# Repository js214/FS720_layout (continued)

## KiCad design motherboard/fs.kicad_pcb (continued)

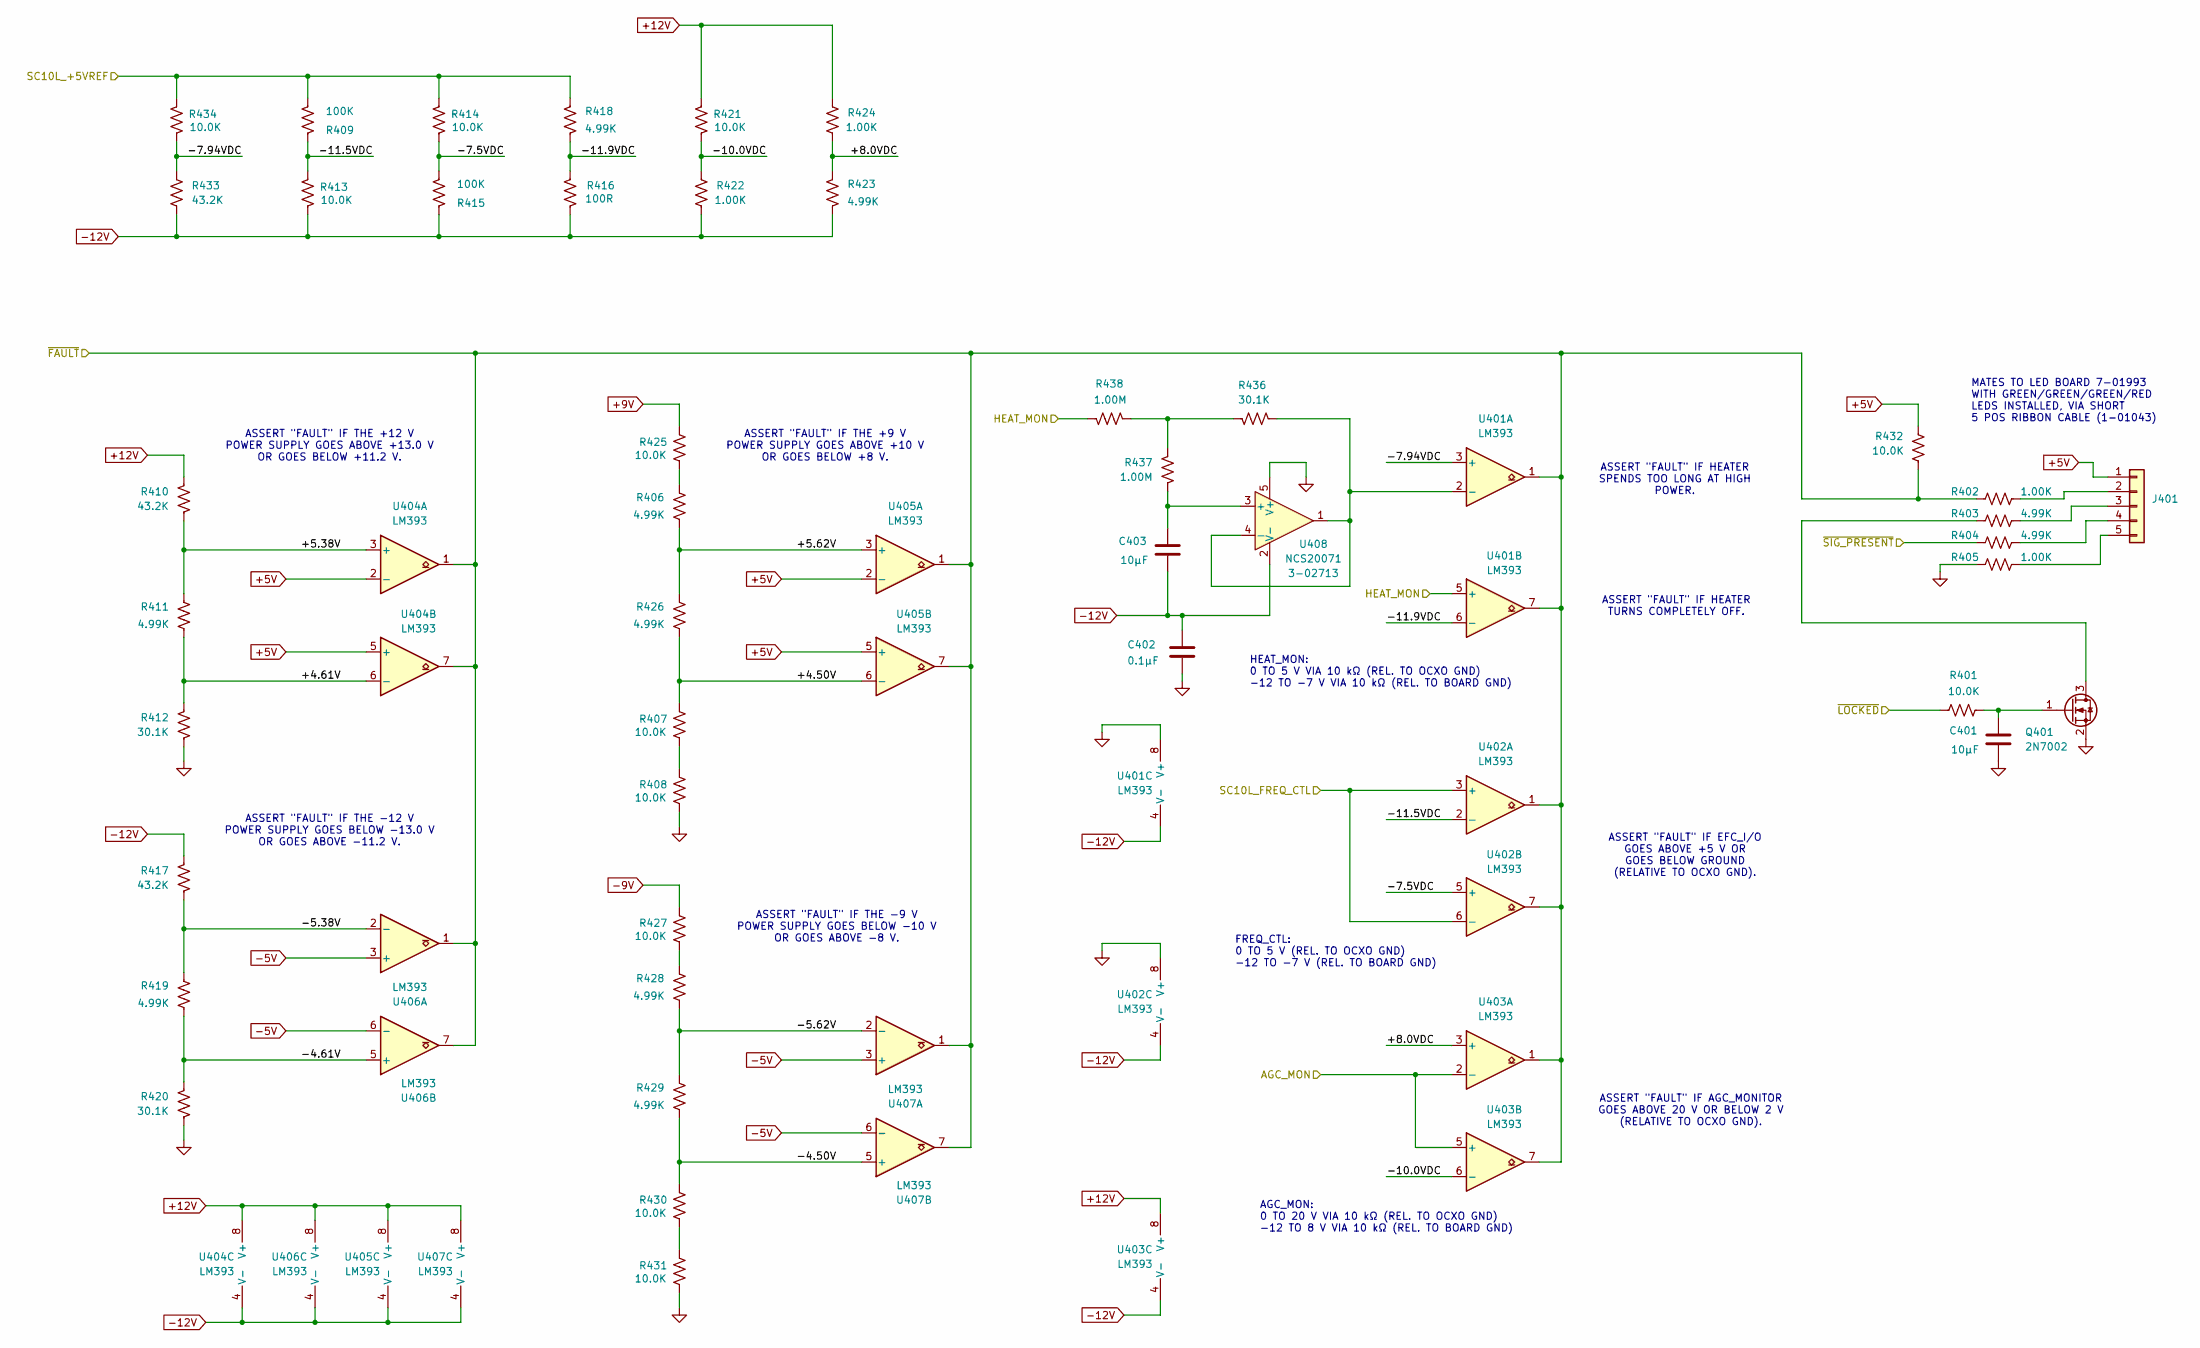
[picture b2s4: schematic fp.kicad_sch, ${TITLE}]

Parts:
C401, C403: 10μF; C_0805_2012Metric; Voltage 25V; MPN GRM21BR61E106KA73L; JLCPCB C84416
C402: 0.1μF; C_0603_1608Metric; Voltage 50V; MPN 06035C104KAT4A; JLCPCB C14663
J401: Conn_01x05; PinHeader_1x05_P2.54mm_Vertical; MPN --; JLCPCB --
Q401: 2N7002; SOT-23; MPN 2N7002H6327XTSA2; JLCPCB C8545
R401, R407, R408, R413, R414, R421, R425, R427, R430, R431, R432, R434: 10.0K; R_0603_1608Metric; MPN TFCR0603-16W-E-1002FT; JLCPCB C98220
R402, R405, R422, R424: 1.00K; R_0603_1608Metric; MPN RR0816P-102-D; JLCPCB C22548
R403, R404, R406, R411, R418, R419, R423, R426, R428, R429: 4.99K; R_0603_1608Metric; MPN TFCR0603-16W-E-4991FT; JLCPCB C23046
R409, R415: 100K; R_0603_1608Metric; MPN TFCR0603-16W-E-1003FT; JLCPCB C25803
R410, R417, R433: 43.2K; R_0603_1608Metric; MPN TNPW060343K2BEEA; JLCPCB C23053
R412, R420, R436: 30.1K; R_0603_1608Metric; MPN RR0816P-3012-D-47C; JLCPCB C23000
R416: 100R; R_0603_1608Metric; MPN RR0816P-101-D; JLCPCB C22775
R437, R438: 1.00M; R_0603_1608Metric; MPN RMCF0603FT1M00; JLCPCB C22935
U401, U402, U403, U404, U405, U406, U407: LM393; SO-8_3.9x4.9mm_P1.27mm; MPN LM393DR; JLCPCB C67470
U408: NCS20071; TSOT-23-5; MPN NCS20071SN2T1G; JLCPCB C457774

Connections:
+5V: J401.1, R432.1, U404.2 (-), U404.5 (+), U405.2 (-), U405.5 (+); also elsewhere on the board
+9V: R425.1; also elsewhere on the board
+12V: R410.2, R421.1, R424.2, U403.8 (V+), U404.8 (V+), U405.8 (V+), U406.8 (V+), U407.8 (V+); also elsewhere on the board
-5V: U406.3 (+), U406.6 (-), U407.3 (+), U407.6 (-); also elsewhere on the board
-9V: R427.1; also elsewhere on the board
-12V: C402.1, C403.2, R413.2, R415.1, R416.2, R417.2, R422.1, R423.1, R433.1, U401.4 (V-), U402.4 (V-), U403.4 (V-), U404.4 (V-), U405.4 (V-), U406.4 (V-), U407.4 (V-), U408.2 (V-); also elsewhere on the board
/AGC_MON: U403.2 (-), U403.5 (+); also elsewhere on the board
/Front Panel/+4.50V: R407.1, R426.1, U405.6 (-)
/Front Panel/+4.61V: R411.1, R412.2, U404.6 (-)
/Front Panel/+5.38V: R410.1, R411.2, U404.3 (+)
/Front Panel/+5.62V: R406.1, R426.2, U405.3 (+)
/Front Panel/+8.0VDC: R423.2, R424.1, U403.3 (+)
/Front Panel/-4.50V: R429.1, R430.1, U407.5 (+)
/Front Panel/-4.61V: R419.1, R420.2, U406.5 (+)
/Front Panel/-5.38V: R417.1, R419.2, U406.2 (-)
/Front Panel/-5.62V: R428.1, R429.2, U407.2 (-)
/Front Panel/-7.5VDC: R414.2, R415.2, U402.5 (+)
/Front Panel/-7.94VDC: R433.2, R434.2, U401.3 (+)
/Front Panel/-10.0VDC: R421.2, R422.2, U403.6 (-)
/Front Panel/-11.5VDC: R409.1, R413.1, U402.2 (-)
/Front Panel/-11.9VDC: R416.1, R418.1, U401.6 (-)
/HEAT_MON: R438.2, U401.5 (+); also elsewhere on the board
/SC10L_+5VREF: R409.2, R414.1, R418.2, R434.1; also elsewhere on the board
/SC10L_FREQ_CTL: U402.3 (+), U402.6 (-); also elsewhere on the board
/~FAULT: R402.1, R432.2, U401.1, U401.7, U402.1, U402.7, U403.1, U403.7, U404.1, U404.7, U405.1, U405.7, U406.1, U406.7, U407.1, U407.7; also elsewhere on the board
/~LOCKED: R401.1; also elsewhere on the board
/~SIG_PRESENT: R404.1; also elsewhere on the board
GND: C401.2, C402.2, Q401.2 (S), R405.1, R408.2, R412.1, R420.1, R431.2, U401.8 (V+), U402.8 (V+), U408.5 (V+); also elsewhere on the board
unnamed: J401.2, R402.2
unnamed: J401.3, R403.2
unnamed: J401.4, R404.2
unnamed: J401.5, R405.2
unnamed: Q401.3 (D), R403.1
unnamed: C401.1, Q401.1 (G), R401.2
unnamed: R406.2, R425.2
unnamed: R407.2, R408.1
unnamed: R427.2, R428.2
unnamed: R430.2, R431.1
unnamed: R436.1, R437.2, R438.1
unnamed: R436.2, U401.2 (-), U408.1, U408.4 (-)
unnamed: C403.1, R437.1, U408.3 (+)

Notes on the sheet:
ASSERT "FAULT" IF THE -12 V POWER SUPPLY GOES BELOW -13.0 V OR GOES ABOVE -11.2 V.
AGC_MON: 0 TO 20 V VIA 10 kΩ (REL. TO OCXO GND) -12 TO 8 V VIA 10 kΩ (REL. TO BOARD GND)
ASSERT "FAULT" IF EFC_I/O GOES ABOVE +5 V OR GOES BELOW GROUND (RELATIVE TO OCXO GND).
ASSERT "FAULT" IF THE +12 V POWER SUPPLY GOES ABOVE +13.0 V OR GOES BELOW +11.2 V.
ASSERT "FAULT" IF THE -9 V POWER SUPPLY GOES BELOW -10 V OR GOES ABOVE -8 V.
HEAT_MON: 0 TO 5 V VIA 10 kΩ (REL. TO OCXO GND) -12 TO -7 V VIA 10 kΩ (REL. TO BOARD GND)
ASSERT "FAULT" IF HEATER SPENDS TOO LONG AT HIGH POWER.
ASSERT "FAULT" IF THE +9 V POWER SUPPLY GOES ABOVE +10 V OR GOES BELOW +8 V.
ASSERT "FAULT" IF HEATER TURNS COMPLETELY OFF.
FREQ_CTL: 0 TO 5 V (REL. TO OCXO GND) -12 TO -7 V (REL. TO BOARD GND)
MATES TO LED BOARD 7-01993 WITH GREEN/GREEN/GREEN/RED LEDS INSTALLED, VIA SHORT 5 POS RIBBON CABLE (1-01043)
ASSERT "FAULT" IF AGC_MONITOR GOES ABOVE 20 V OR BELOW 2 V (RELATIVE TO OCXO GND).

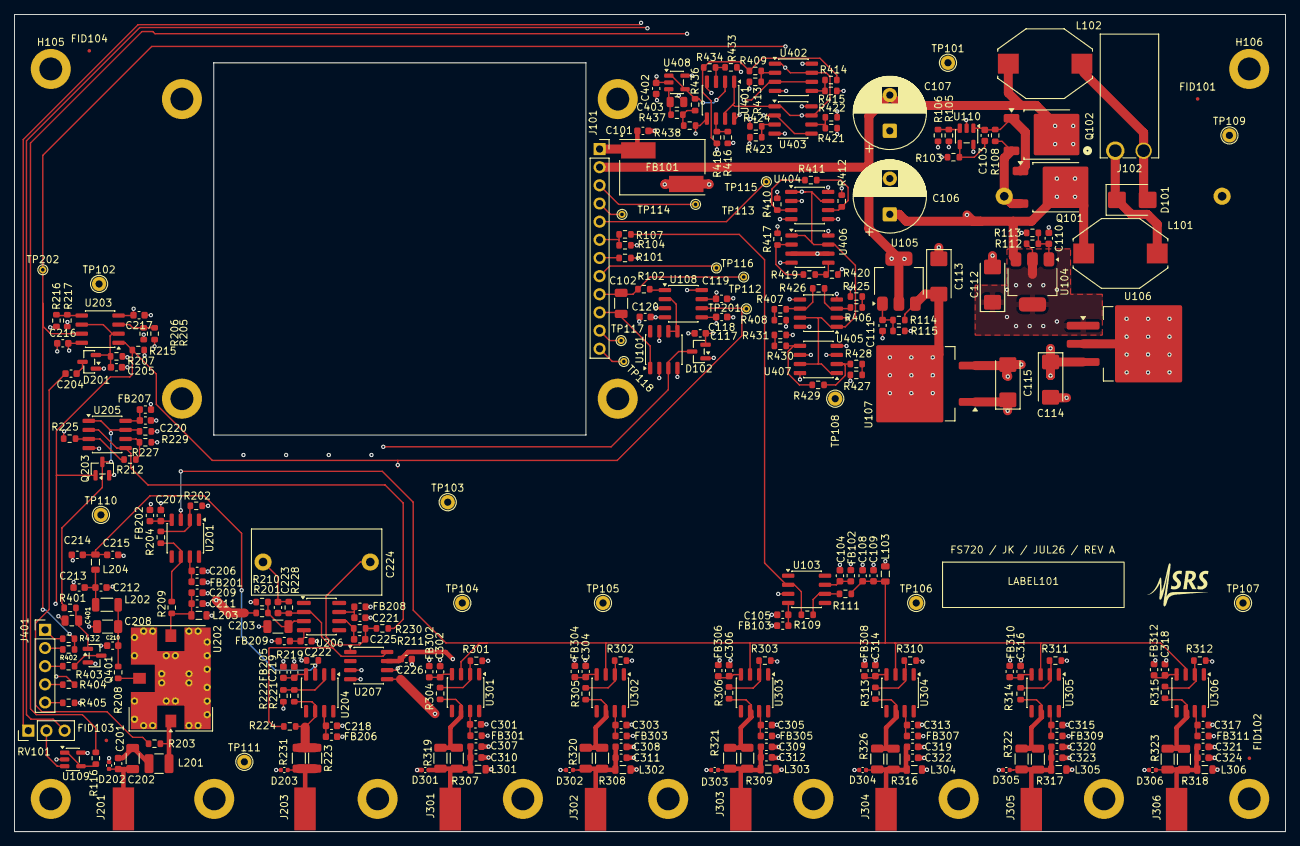
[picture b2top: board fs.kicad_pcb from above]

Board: 6 copper layers, 177.8 x 114.3 mm, 307 parts (1 on the bottom side), 128 nets.

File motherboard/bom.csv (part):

"Designator","Qty","Value","Exclude from BOM","Footprint","MPN","JLCPCB Part #","SRS PN","Voltage","Description"
"C101,C104,C105,C110,C111,C117,C118,C119,C120,C205,C206,C207,C216,C217,C218,C219,C220,C221,C222,C226,C301,C302,C303,C304,C305,C306,C313,C314,C315,C316,C317,C318,C402","33","0.1μF","","Capacitor_SMD:C_0603_1608Metric","06035C104KAT4A","C14663","5-00764","50V","Capacitor, Mono, 50V,+/-10%, X7R, 0603"
"C102,C203","2","0.1μF C0G","","Capacitor_SMD:C_1206_3216Metric","GRT31C5C1H104FA02L","C3839854","5-01075","50V","Cap Ceramic 0.1uF 50V C0G 1% Pad SMD 1206 125°C Automotive AEC-Q200 T/R"
"C103,C204,C212,C214,C223,C225","6","1nF NP0","","Capacitor_SMD:C_0603_1608Metric","C0603C102J5GACTU","C2181873","5-00740","50V","Capacitor, Mono, 50V, ¦0.25pF or 5%, NPO, 0603, 1000P"
"C106,C107","2","330μF","","Capacitor_THT:CP_Radial_D10.0mm_P5.00mm","EEU-FC1V331","EEU-FC1V331","5-00516","35V","Capacitor, Electrolytic, High Ripple, High Temp (-55/+105 DEG C)"
"C108,C209,C307,C308,C309,C319,C320,C321","8","47pF","","Capacitor_SMD:C_0603_1608Metric","C0603C470J5GACTU","C2167347","5-00708","50V","Capacitor, Mono, 50V, ¦0.25pF or 5%, NPO, 0603"
"C109,C211,C310,C311,C312,C322,C323,C324","8","120pF","","Capacitor_SMD:C_0603_1608Metric","C0603C121J5GACTU","C2168575","5-00718","50V","CAP CER 120PF 50V C0G/NP0 0603"
"C112,C113,C114,C115","4","4.7μF-T35","","Capacitor_Tantalum_SMD:CP_EIA-6032-15_Kemet-U","TAJC475M035RNJ","C11378","5-00520","35V","SMD TANTALUM, C-Case"
"C201,C213","2","270pF","","Capacitor_SMD:C_0603_1608Metric","C0603C271J5GACTU","C49326315","5-00726","50V","Capacitor, Mono, 50V, ¦0.25pF or 5%, NPO, 0603"
"C202,C208","2","180pF","","Capacitor_SMD:C_1206_3216Metric","C1206C181J5GACTU","C541494","5-00378","50V","Capacitor, Mono, 50V, 5%, NPO, 1206"
"C210","1","100pF","","Capacitor_SMD:C_0603_1608Metric","C0603C101J5GACTU","C2167328","5-00716","50V","Capacitor, Mono, 50V, ¦0.25pF or 5%, NPO, 0603"
"C215","1","390pF","","Capacitor_SMD:C_0603_1608Metric","C0603C391J5GACTU","C22408867","5-00730","50V","Capacitor, Mono, 50V, ¦0.25pF or 5%, NPO, 0603"
"C224","1","10μF PET","","Capacitor_THT:C_Rect_L18.0mm_W9.0mm_P15.00mm_FKS3_FKP3","B32522C0106K189","C3769153","5-00959","63V","10uF Polyester Cap"
"C401,C403","2","10μF","","Capacitor_SMD:C_0805_2012Metric","GRM21BR61E106KA73L","C84416","5-00954","25V","10 uF 0805 capacitor, 25V X5R 10%"
"D101","1","MBRS230LT3G","","Diode_SMD:D_SMB","MBRS230LT3G  ","C236135","3-02091","","DIODE Schottky 30V 2A"
"D102,D201","2","MMBD352LT1G","","Package_TO_SOT_SMD:SOT-23","MMBD352LT1G","C463549","3-00538","","MMBD352L, DUAL SCHOTTKY DIODE"
"D202,D203,D301,D302,D303,D304,D305,D306","8","14V TVS","","Capacitor_SMD:C_0402_1005Metric","PESD0402-140","C7473167","3-02609","","TVS DIODE 14V 40V 0402"
"FB101","1","9.5A BEAD","","INDUCTOR_SRS:SMB2.5R-2","SMB2.5R-2","C3716465","6-01322","","Ferrite bead,SMB, 9500 mA, 490 ohms@100 MHz, 0.005 ohm@DC, SMB2.5R-2"
"FB102,FB103,FB201,FB202,FB205,FB206,FB207,FB208,FB209,FB301,FB302,FB303,FB304,FB305,FB306,FB307,FB308,FB309,FB310,FB311,FB312","21","742863160","","Inductor_SMD:L_0603_1608Metric","742863160","C2650942","6-01344","","0603 Ferrite bead, 400 mA"
"J101","1","Header","","Connector_PinSocket_2.54mm:PinSocket_1x12_P2.54mm_Vertical","1-215299-2","C7155422","1-01602","","Generic connector, single row, 01x12, script generated (kicad-library-utils/schlib/autogen/connector/)"
"J102","1","640389-2","","CONNECTOR_SRS:640389-2_TYC","640389-2","C305837","1-00469","","Header, SIM, Right Angle, Polarized"
"J201,J203,J301,J302,J303,J304,J305,J306","8","BNC","","CONNECTOR_SRS:BNC-STRIP","73100-0195","--","1-01158","","Conn BNC 50Ohm Solder Pot ST Panel Mount RCP Gold Bag"
"L101,L102","2","47μH","","INDUCTOR_SRS:PM3316","PM3316-470M-RC","C1329573","6-00791","","RF Choke Wirewound 47uH 10% 1KHz 30Q-Factor Ferrite 790mA 170mOhm DCR RDL Bag"
"L103,L203,L301,L302,L303,L304,L305,L306","8","1.5μH","","Inductor_SMD:L_0805_2012Metric","MLF2012A1R5JTD25","C139220,C76794","6-01142","","FIXED IND 1.5UH 80MA 400 MOHM 0805"
"L201","1","0.56μH","","Inductor_SMD:L_1210_3225Metric","1206CS-561XJRC","C318049","6-00595","","Inductor RF Chip Unshielded Wirewound 0.56uH 5% 35MHz 45Q-Factor Ceramic 0.46A 1.34Ohm DCR 1206 Automotive AEC-Q200 T/R"
"L202","1","8.2μH","","Inductor_SMD:L_1206_3216Metric","AIML-1206-8R2K-T","C51018442","6-01361","","Inductor"
"L204","1","15μH","","Inductor_SMD:L_0805_2012Metric","MLF2012C150K","C383402","6-01078","","0805 chip inductor"
"LABEL101","1","Label","","MECHANICAL_SRS:LABEL_1in_0.25in","10011975","--","9-01776","","LABEL STOCK, POLYESTER, GLOSS WHITE, 1"" x 0.25"""
"PCB101","1","PCB","","","--","--","","","Printed Circuit Board"
"Q101","1","MJD44H11","","Package_TO_SOT_SMD:TO-252-2","MJD44H11G","C36608","3-01091","","Trans GP BJT NPN 80V 16A 1750mW Automotive 3-Pin(2+Tab) DPAK Tube"
"Q102","1","MJD45H11","","Package_TO_SOT_SMD:TO-252-2","MJD45H11G","C5424","3-01100","","Trans GP BJT PNP 80V 16A 1750mW Automotive 3-Pin(2+Tab) DPAK Tube"
"Q203,Q401","2","2N7002","","Package_TO_SOT_SMD:SOT-23","2N7002H6327XTSA2","C8545","3-02247","","0.115A Id, 60V Vds, N-Channel MOSFET, SOT-23"
"R101,R111,R208,R209","4","49.9R","","Resistor_SMD:R_0603_1608Metric","TFCR0603-16W-E-49R9FT","C23185","4-02032","","Resistor, Thin Film, 1%, 50 ppm, 1/16W 0603 Chip"
"R102,R108,R206,R416","4","100R","","Resistor_SMD:R_0603_1608Metric","RR0816P-101-D","C22775","4-02061","","Resistor, Thin Film, 1%, 50 ppm, 1/16W 0603 Chip"
"R103,R116,R203,R211,R225,R227,R402,R405,R422,R424","10","1.00K","","Resistor_SMD:R_0603_1608Metric","RR0816P-102-D","C22548","4-02157","","Resistor, Thin Film, 1%, 50 ppm, 1/16W 0603 Chip, 1.00K"
"R104","1","61.9R","","Resistor_SMD:R_0603_1608Metric","TFCR0603-16W-E-61R9F","C101138","4-02041","","Resistor, Thin Film, 1%, 50 ppm, 1/16W 0603 Chip"
"R105,R106,R201,R210,R212,R215,R217,R230,R401,R407,R408,R413,R414,R421,R425,R427,R430,R431,R432,R434","20","10.0K","","Resistor_SMD:R_0603_1608Metric","TFCR0603-16W-E-1002FT","C98220","4-02253","","Resistor, Thin Film, 1%, 50 ppm, 1/16W 0603 Chip"
"R107,R112,R114,R202,R301,R302,R303,R310,R311,R312","10","249R","","Resistor_SMD:R_0603_1608Metric","TFCR0603-16W-E-2490FT","C22919","4-02099","","Resistor, Thin Film, 1%, 50 ppm, 1/16W 0603 Chip"
"R109","1","162R","","Resistor_SMD:R_0603_1608Metric","TFCR0603-16W-E-1620F","C185368","4-02081","","Resistor, Thin Film, 1%, 50 ppm, 1/16W 0603 Chip"
"R110","1","18R 5W","","Resistor_THT:R_Axial_Power_L25.0mm_W9.0mm_P30.48mm","CW00518R00JE12","--","4-00320","","Resistor, Wire-wound"
"R113","1","1.54K","","Resistor_SMD:R_0603_1608Metric","TFCR0603-16W-E-1541F","C22842","4-02175","","Resistor, Thin Film, 1%, 50 ppm, 1/16W 0603 Chip"
"R115","1","1.50K","","Resistor_SMD:R_0603_1608Metric","TFCR0603-16W-E-1501FT","C22843","4-02174","","Resistor, Thin Film, 1%, 50 ppm, 1/16W 0603 Chip"
"R204,R219,R304,R305,R306,R313,R314,R315","8","499R","","Resistor_SMD:R_0603_1608Metric","TFCR0603-16W-E-4990FT","C23065","4-02128","","Resistor, Thin Film, 1%, 50 ppm, 1/16W 0603 Chip"
"R205","1","2.74K","","Resistor_SMD:R_0603_1608Metric","TFCR0603-16W-E-2741FT","C2930073","4-02199","","Resistor, Thin Film, 1%, 50 ppm, 1/16W 0603 Chip"
"R207,R229,R409,R415","4","100K","","Resistor_SMD:R_0603_1608Metric","TFCR0603-16W-E-1003FT","C25803","4-02349","","Resistor, Thin Film, 1%, 50 ppm, 1/16W 0603 Chip"
"R216,R412,R420,R436","4","30.1K","","Resistor_SMD:R_0603_1608Metric","RR0816P-3012-D-47C","C23000","4-02299","","Resistor, Thin Film, 1%, 50 ppm, 1/16W 0603 Chip"
"R221","1","374R","","Resistor_SMD:R_0603_1608Metric","TFCR0603-16W-E-3740F","C3981304","4-02116","","Resistor, Thin Film, 1%, 50 ppm, 1/16W 0603 Chip"
"R222","1","24.9R","","Resistor_SMD:R_0603_1608Metric","TFCR0603-16W-E-24R9FT","C22916","4-02003","","Resistor, Thin Film, 1%, 50 ppm, 1/16W 0603 Chip"
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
